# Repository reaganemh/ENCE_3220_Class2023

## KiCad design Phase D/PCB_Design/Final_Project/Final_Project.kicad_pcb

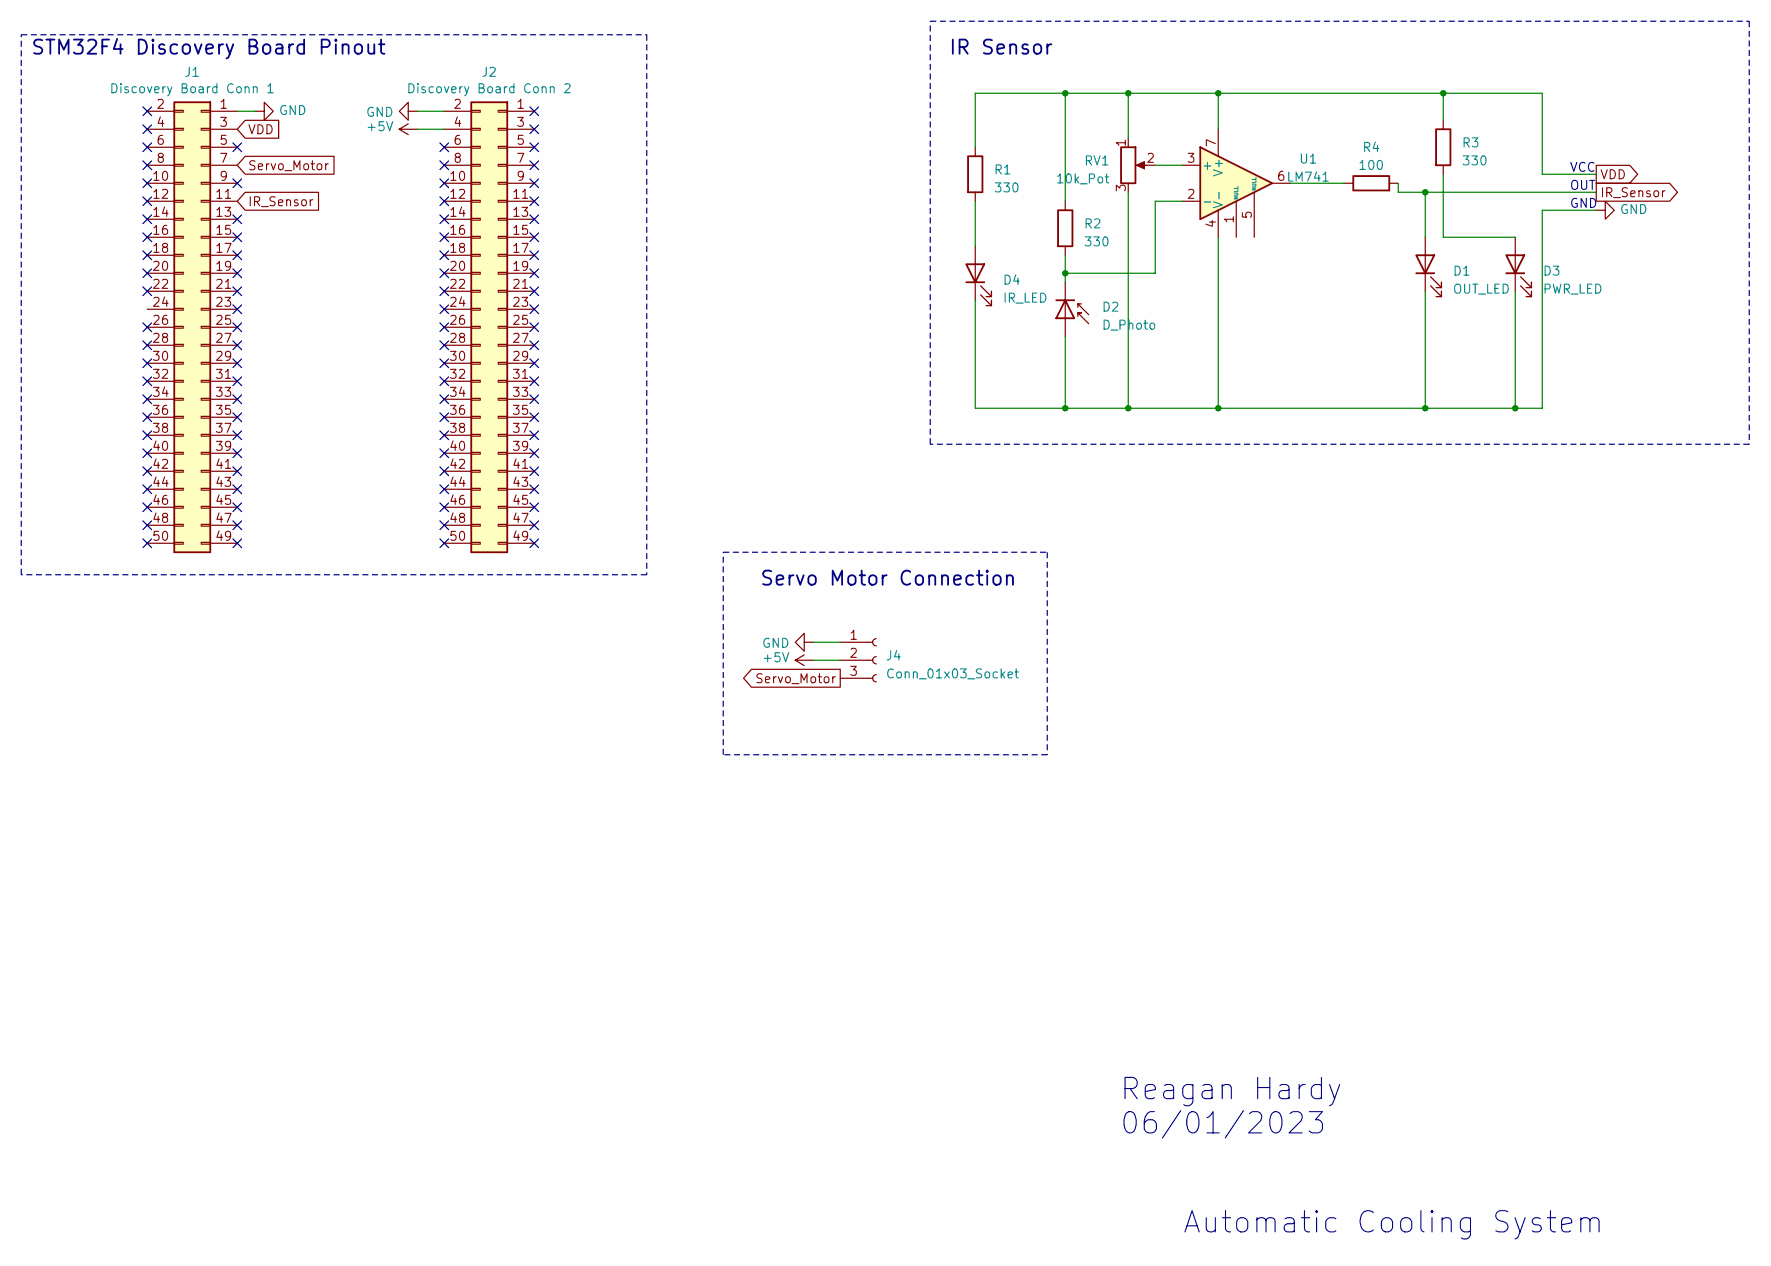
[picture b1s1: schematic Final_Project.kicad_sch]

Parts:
D1: OUT_LED; LED_0805_2012Metric_Pad1.15x1.40mm_HandSolder
D2: D_Photo; LED_D5.0mm_Horizontal_O1.27mm_Z3.0mm
D3: PWR_LED; LED_0805_2012Metric_Pad1.15x1.40mm_HandSolder
D4: IR_LED; LED_D5.0mm_Horizontal_O1.27mm_Z3.0mm
J1: Discovery Board Conn 1; PinSocket_2x25_P2.54mm_Vertical
J2: Discovery Board Conn 2; PinSocket_2x25_P2.54mm_Vertical
J4: Conn_01x03_Socket; PinSocket_1x03_P2.54mm_Vertical
R1, R2, R3: 330; R_0805_2012Metric
R4: 100; R_0805_2012Metric
RV1: 10k_Pot; Potentiometer_ACP_CA9-V10_Vertical_Hole
U1: LM741; SOIC-8_3.9x4.9mm_P1.27mm

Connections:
+5V: J2.4, J4.2
GND: D1.1 (K), D2.2 (A), D3.1 (K), D4.1 (K), J1.1, J2.2, J4.1, RV1.3, U1.4 (V-)
IR_Sensor: D1.2 (A), J1.11, R4.2
unnamed: D2.1 (K), R2.2, U1.2 (-)
unnamed: D3.2 (A), R3.2
unnamed: D4.2 (A), R1.2
unnamed: R4.1, U1.6
unnamed: RV1.2, U1.3 (+)
Servo_Motor: J1.7, J4.3
VDD: J1.3, R1.1, R2.1, R3.1, RV1.1, U1.7 (V+)

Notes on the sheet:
Automatic Cooling System
IR Sensor
Reagan Hardy 06/01/2023
VCC
GND
STM32F4 Discovery Board Pinout
Servo Motor Connection
OUT

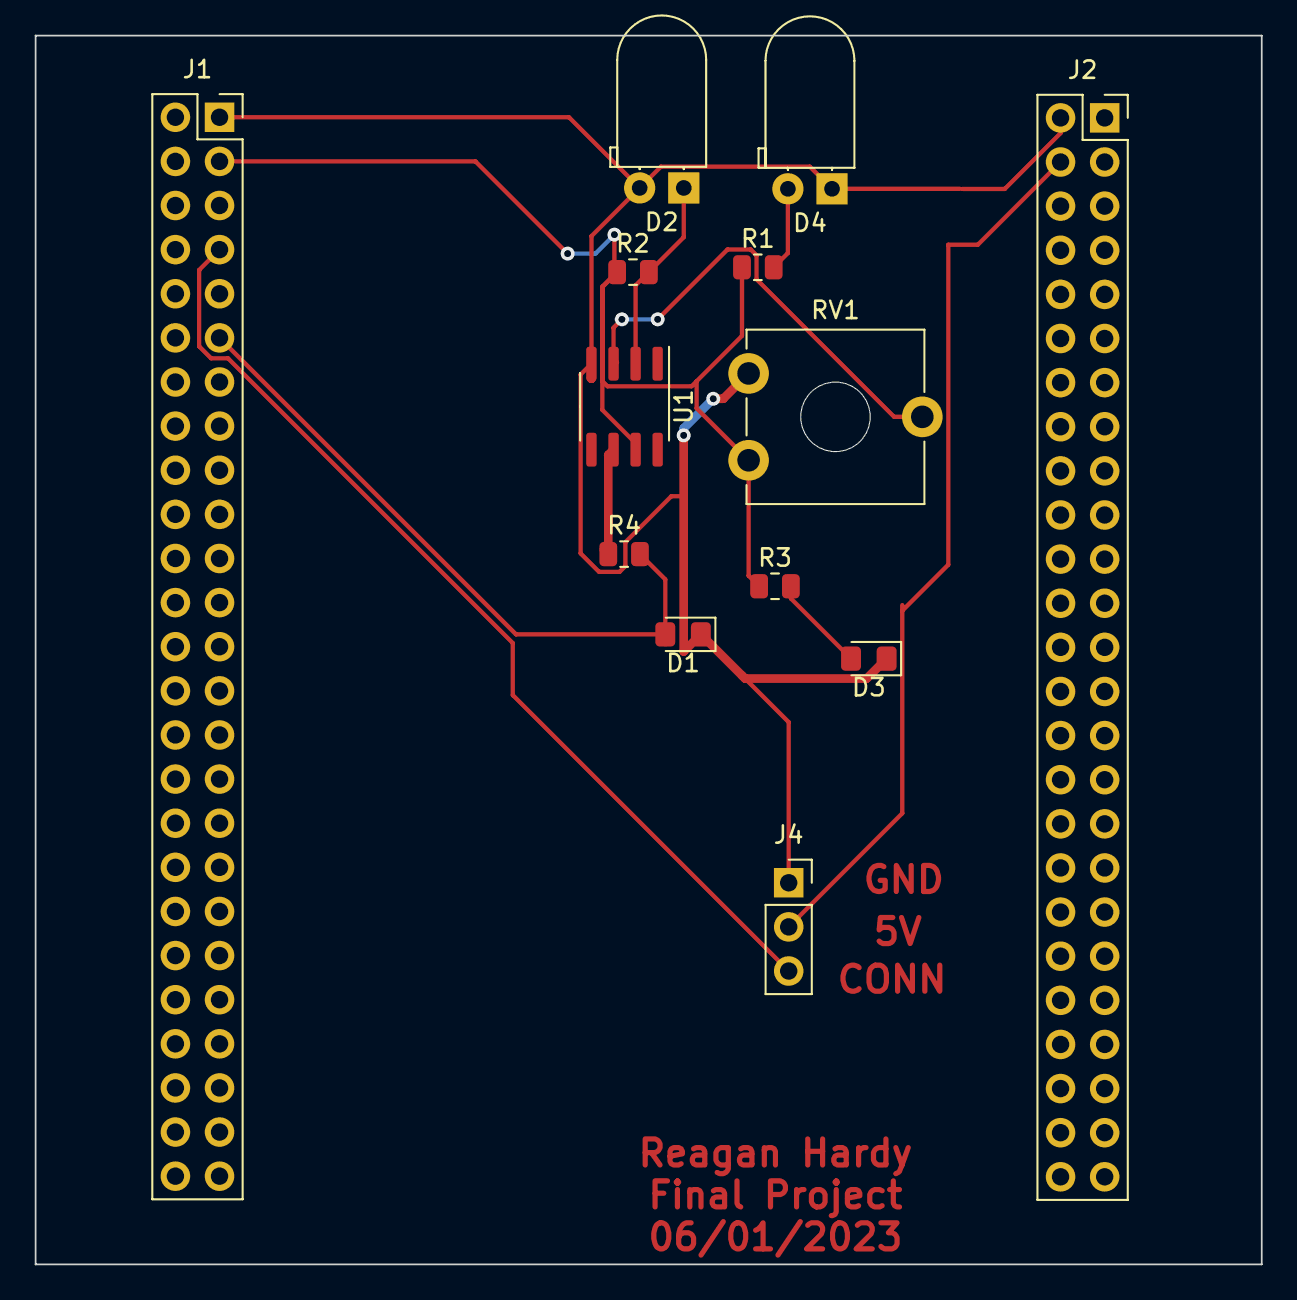
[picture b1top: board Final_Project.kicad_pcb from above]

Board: 2 copper layers, 70.6 x 70.7 mm, 13 parts (0 on the bottom side), 10 nets.

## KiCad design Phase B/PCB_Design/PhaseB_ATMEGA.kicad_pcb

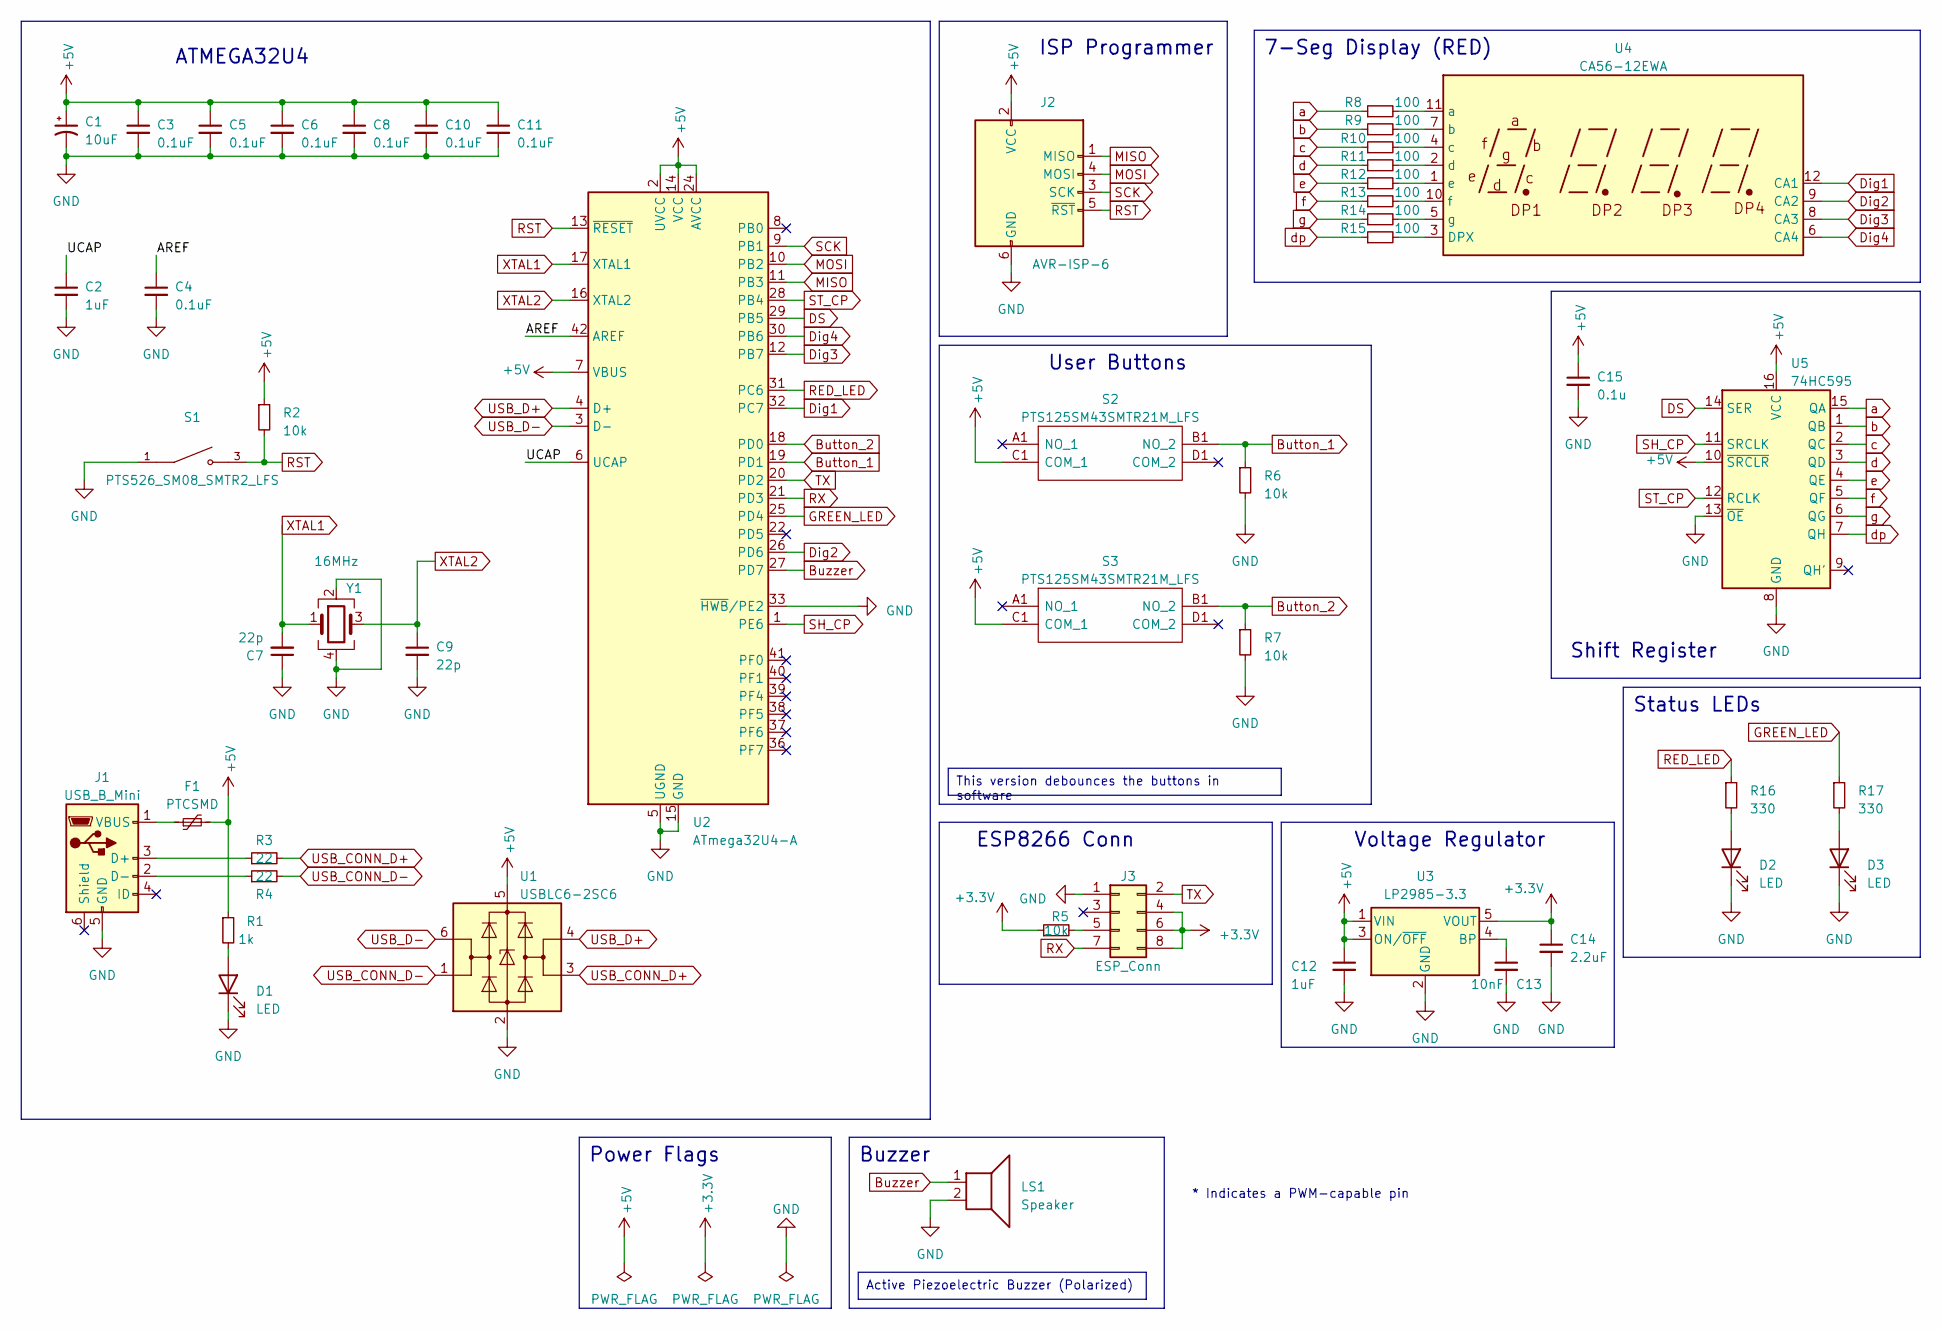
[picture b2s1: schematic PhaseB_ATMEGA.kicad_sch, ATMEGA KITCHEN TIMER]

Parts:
C1: 10uF; C_0805_2012Metric
C2, C12: 1uF; C_0603_1608Metric
C3, C4, C5, C6, C8, C10, C11: 0.1uF; C_0603_1608Metric
C7, C9: 22p; C_0603_1608Metric
C13: 10nF; C_0603_1608Metric
C14: 2.2uF; C_0603_1608Metric
C15: 0.1u; C_0603_1608Metric
D1, D2, D3: LED; LED_0805_2012Metric
F1: PTCSMD; Fuse_1812_4532Metric
J1: USB_B_Mini; USB_Mini-B_Lumberg_2486_01_Horizontal
J2: AVR-ISP-6; PinSocket_2x03_P2.54mm_Vertical
J3: ESP_Conn; PinSocket_2x04_P2.54mm_Vertical
LS1: Speaker; Buzzer_12x9.5RM7.6
R1: 1k; R_0603_1608Metric
R2, R5: 10k; R_0603_1608Metric
R3, R4: 22; R_0603_1608Metric
R6, R7: 10k; R_0805_2012Metric
R8, R9, R10, R11, R12, R13, R14, R15: 100; R_0805_2012Metric
R16, R17: 330; R_0805_2012Metric
S1: PTS526_SM08_SMTR2_LFS; PTS526_SMD_Button; PARTREV 20 mar 19
S2, S3: PTS125SM43SMTR21M_LFS; PTS125_SMD_Button; Manufacturer_Part_Number PTS125SM43SMTR21M LFS; Mouser Part Number 611-PTS125S43SMTRLFS
U1: USBLC6-2SC6; SOT-23-6
U2: ATmega32U4-A; TQFP-44_10x10mm_P0.8mm
U3: LP2985-3.3; SOT-23-5
U4: CA56-12EWA
U5: 74HC595; TSSOP-16_4.4x5mm_P0.65mm
Y1: 16MHz; Crystal_SMD_Abracon_ABM8G-4Pin_3.2x2.5mm

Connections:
+3.3V: C14.1, J3.4, J3.6, J3.8, R5.1, U3.5 (VOUT)
+5V: C1.1, C3.1, C5.1, C6.1, C8.1, C10.1, C11.1, C12.1, C15.1, F1.2, J2.2 (VCC), R1.1, R2.1, S2.C1 (COM_1), S3.C1 (COM_1), U1.5 (VBUS), U2.2 (UVCC), U2.7 (VBUS), U2.14 (VCC), U2.24 (AVCC), U2.34 (VCC), U2.44 (AVCC), U3.1 (VIN), U3.3 (ON/~OFF), U5.10 (~SRCLR), U5.16 (VCC)
/AREF: C4.1, U2.42 (AREF)
/UCAP: C2.1, U2.6 (UCAP)
Button_1: R6.1, S2.B1 (NO_2), U2.19 (PD1)
Button_2: R7.1, S3.B1 (NO_2), U2.18 (PD0)
Buzzer: LS1.1, U2.27 (PD7)
DS: U2.29 (PB5), U5.14 (SER)
Dig1: U2.32 (PC7), U4.12 (CA1)
Dig2: U2.26 (PD6), U4.9 (CA2)
Dig3: U2.12 (PB7), U4.8 (CA3)
Dig4: U2.30 (PB6), U4.6 (CA4)
GND: C1.2, C2.2, C3.2, C4.2, C5.2, C6.2, C7.1, C8.2, C9.2, C10.2, C11.2, C12.2, C13.2, C14.2, C15.2, D1.1 (K), D2.1 (K), D3.1 (K), J1.5 (GND), J2.6 (GND), J3.1, LS1.2, R6.2, R7.2, S1.1, U1.2 (GND), U2.5 (UGND), U2.15 (GND), U2.23 (GND), U2.33 (~HWB/PE2), U2.35 (GND), U2.43 (GND), U3.2 (GND), U5.8 (GND), U5.13 (~OE), Y1.2, Y1.4
GREEN_LED: R17.1, U2.25 (PD4)
MISO: J2.1 (MISO), U2.11 (PB3)
MOSI: J2.4 (MOSI), U2.10 (PB2)
unnamed: D1.2 (A), R1.2
unnamed: D2.2 (A), R16.2
unnamed: D3.2 (A), R17.2
unnamed: J1.3 (D+), R3.1
unnamed: J1.2 (D-), R4.1
unnamed: F1.1, J1.1 (VBUS)
unnamed: J3.5, R5.2
unnamed: C13.1, U3.4 (BP)
unnamed: R15.2, U4.3 (DPX)
unnamed: R8.2, U4.11 (a)
unnamed: R9.2, U4.7 (b)
unnamed: R10.2, U4.4 (c)
unnamed: R11.2, U4.2 (d)
unnamed: R12.2, U4.1 (e)
unnamed: R13.2, U4.10 (f)
unnamed: R14.2, U4.5 (g)
RED_LED: R16.1, U2.31 (PC6)
RST: J2.5 (~RST), R2.2, S1.3, U2.13 (~RESET)
RX: J3.7, U2.21 (PD3)
SCK: J2.3 (SCK), U2.9 (PB1)
SH_CP: U2.1 (PE6), U5.11 (SRCLK)
ST_CP: U2.28 (PB4), U5.12 (RCLK)
TX: J3.2, U2.20 (PD2)
USB_CONN_D+: R3.2, U1.3 (I/O2)
USB_CONN_D-: R4.2, U1.1 (I/O1)
USB_D+: U1.4 (I/O2), U2.4 (D+)
USB_D-: U1.6 (I/O1), U2.3 (D-)
XTAL1: C7.2, U2.17 (XTAL1), Y1.1
XTAL2: C9.1, U2.16 (XTAL2), Y1.3
a: R8.1, U5.15 (QA)
b: R9.1, U5.1 (QB)
c: R10.1, U5.2 (QC)
d: R11.1, U5.3 (QD)
dp: R15.1, U5.7 (QH)
e: R12.1, U5.4 (QE)
f: R13.1, U5.5 (QF)
g: R14.1, U5.6 (QG)

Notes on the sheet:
Active Piezoelectric Buzzer (Polarized)
This version debounces the buttons in software
ATMEGA32U4
Voltage Regulator
ESP8266 Conn
Shift Register
User Buttons
ISP Programmer
Power Flags
Status LEDs
Buzzer
7-Seg Display (RED)
* Indicates a PWM-capable pin

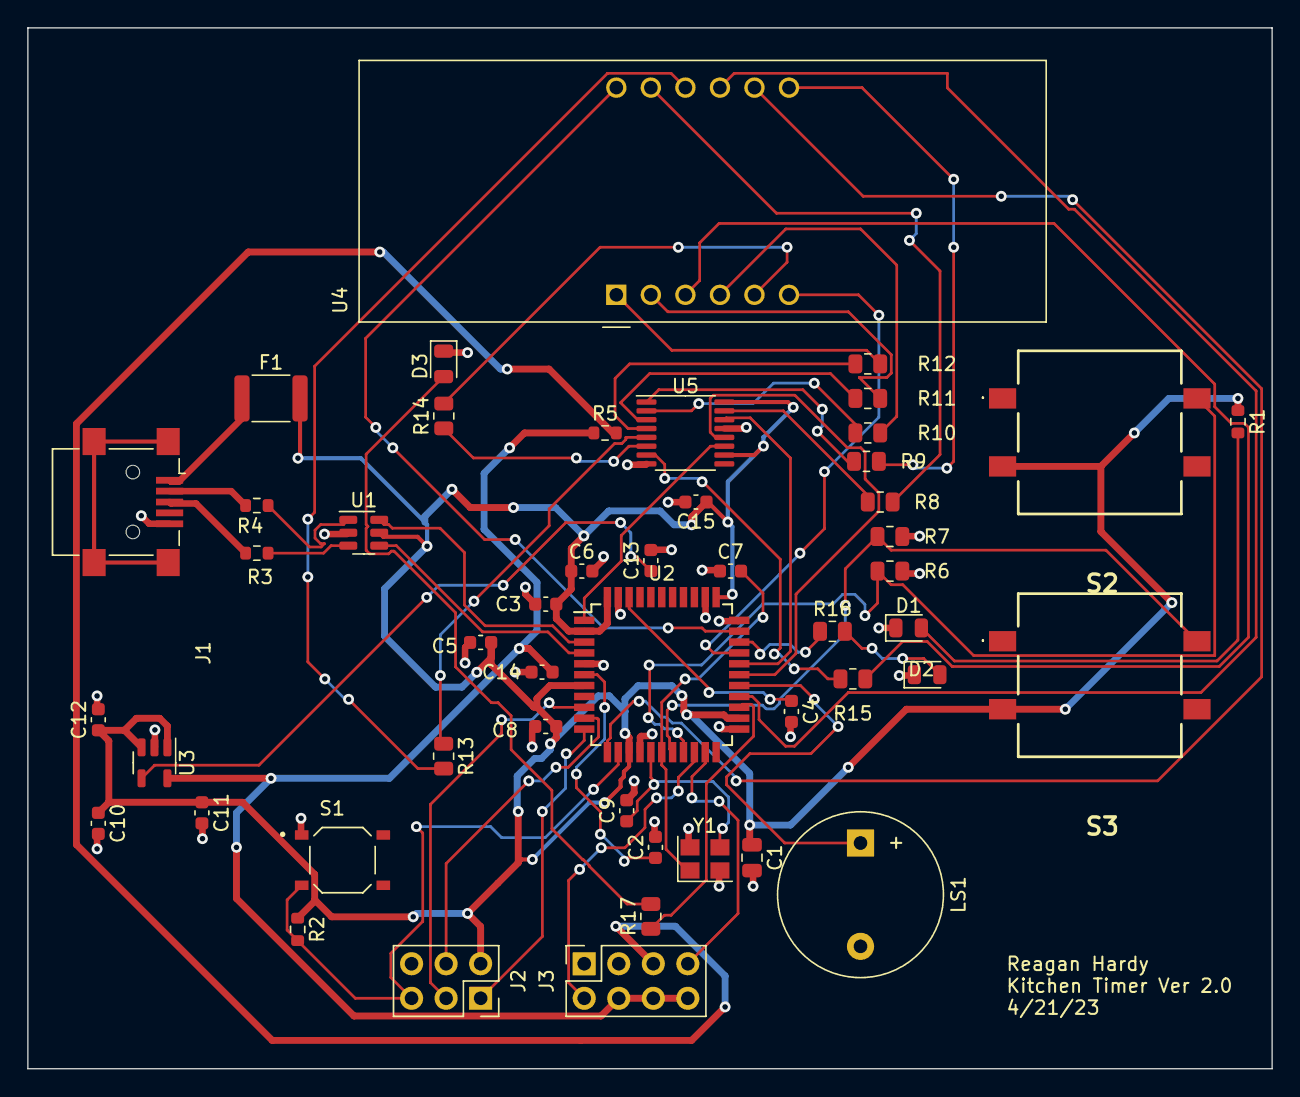
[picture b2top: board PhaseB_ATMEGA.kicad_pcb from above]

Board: 2 copper layers, 91.5 x 76.6 mm, 49 parts (0 on the bottom side), 53 nets.

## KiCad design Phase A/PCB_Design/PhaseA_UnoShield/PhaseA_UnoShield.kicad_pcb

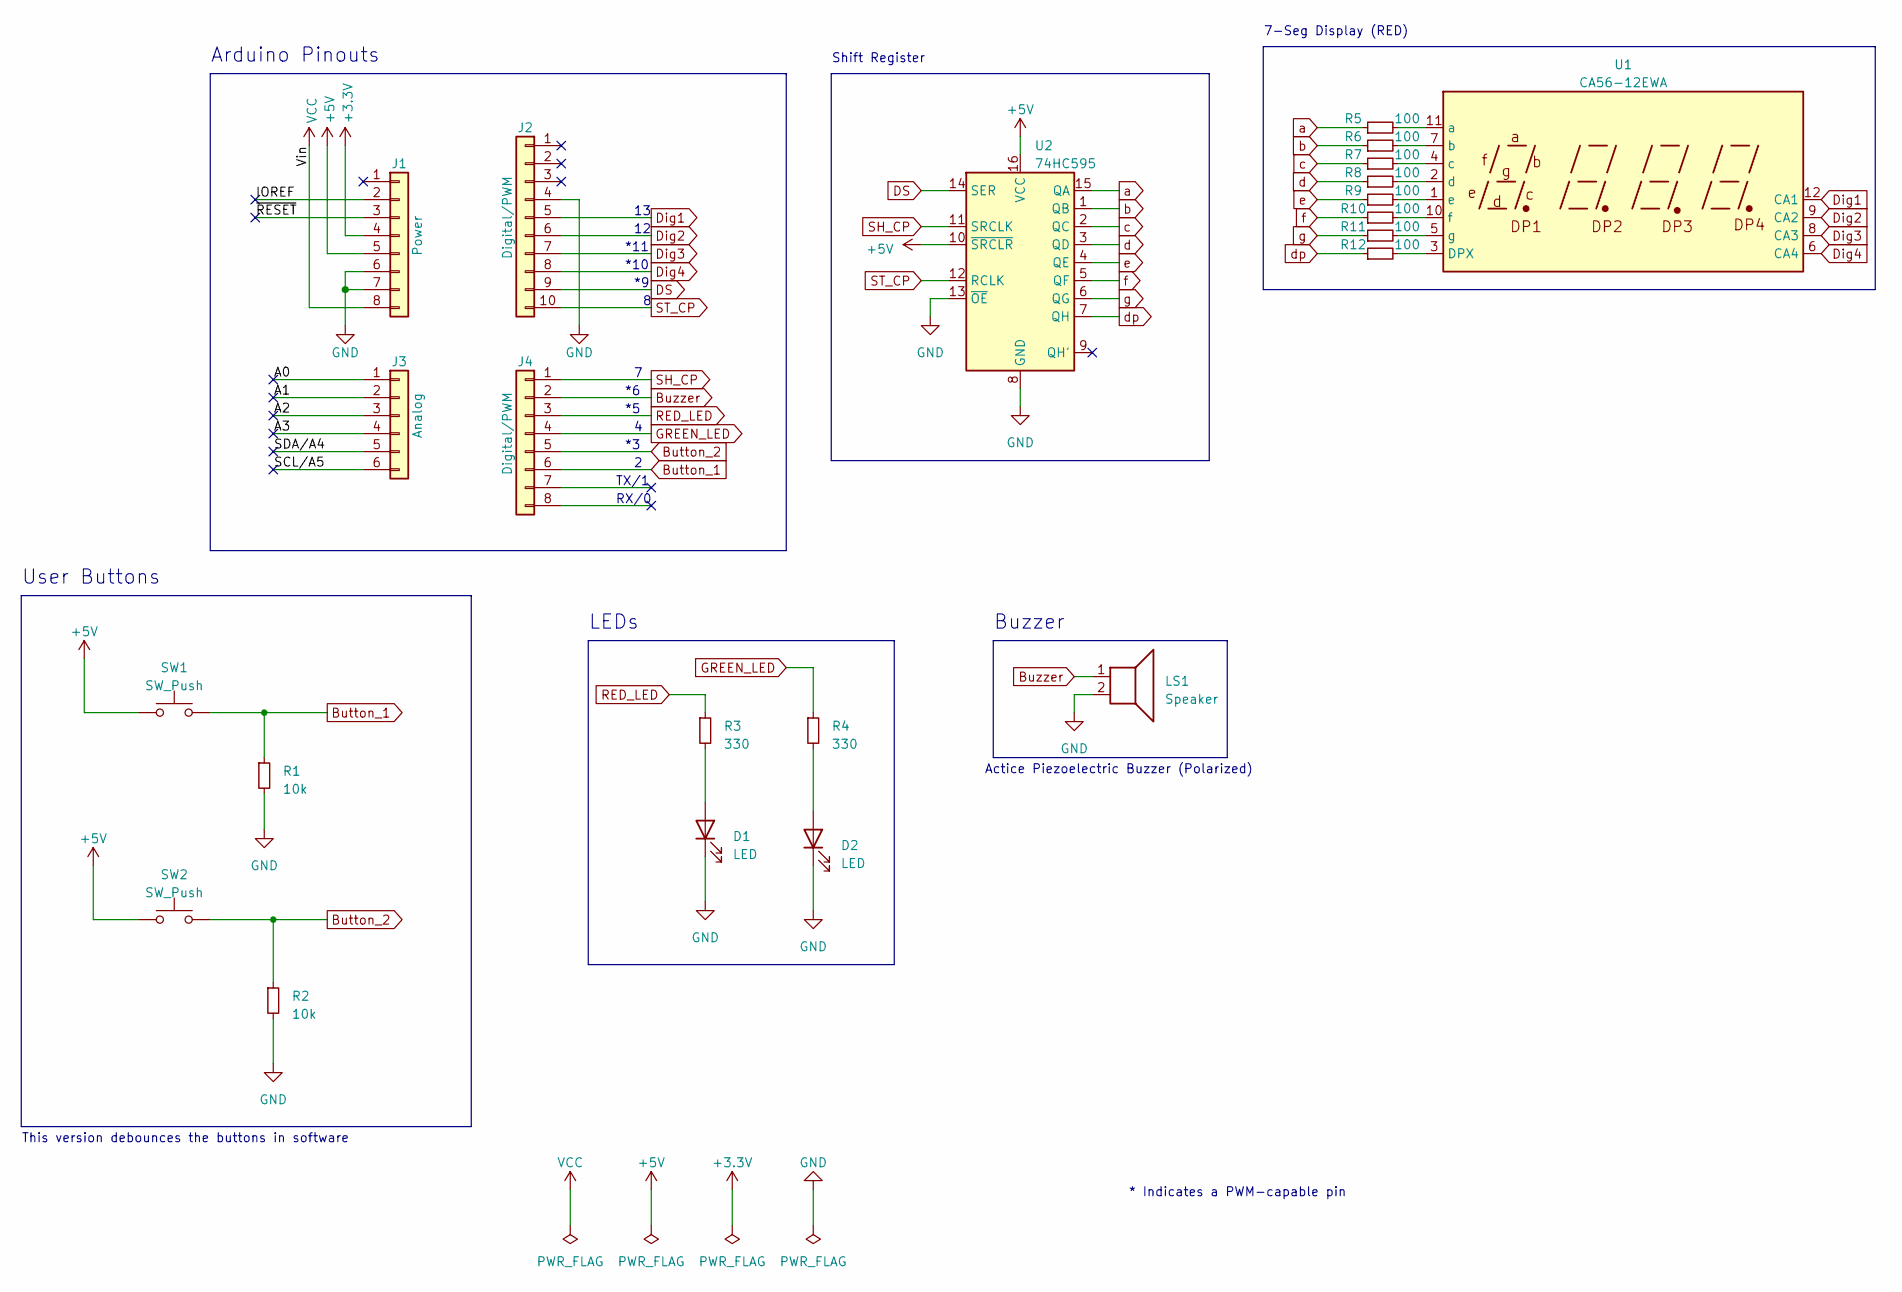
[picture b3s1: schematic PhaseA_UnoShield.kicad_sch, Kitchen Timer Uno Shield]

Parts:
D1, D2: LED; LED_D5.0mm
J1: Power; PinSocket_1x08_P2.54mm_Vertical
J2: Digital/PWM; PinSocket_1x10_P2.54mm_Vertical
J3: Analog; PinSocket_1x06_P2.54mm_Vertical
J4: Digital/PWM; PinSocket_1x08_P2.54mm_Vertical
LS1: Speaker; Buzzer_12x9.5RM7.6
R1, R2: 10k; R_Axial_DIN0207_L6.3mm_D2.5mm_P10.16mm_Horizontal
R3, R4: 330; R_Axial_DIN0207_L6.3mm_D2.5mm_P10.16mm_Horizontal
R5, R6, R7, R8, R9, R10, R11, R12: 100; R_Axial_DIN0207_L6.3mm_D2.5mm_P10.16mm_Horizontal
SW1, SW2: SW_Push; SW_PUSH-12mm
U1: CA56-12EWA
U2: 74HC595; DIP-16_W7.62mm_Socket_LongPads

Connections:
+3V3: J1.4
+5V: J1.5, SW1.1, SW2.1, U2.10 (~SRCLR), U2.16 (VCC)
/A0: J3.1
/A1: J3.2
/A2: J3.3
/A3: J3.4
/IOREF: J1.2
/SCL/A5: J3.6
/SDA/A4: J3.5
/~RESET: J1.3
Button_1: J4.6, R1.1, SW1.2
Button_2: J4.5, R2.1, SW2.2
Buzzer: J4.2, LS1.1
DS: J2.9, U2.14 (SER)
Dig1: J2.5, U1.12 (CA1)
Dig2: J2.6, U1.9 (CA2)
Dig3: J2.7, U1.8 (CA3)
Dig4: J2.8, U1.6 (CA4)
GND: D1.1 (K), D2.1 (K), J1.6, J1.7, J2.4, LS1.2, R1.2, R2.2, U2.8 (GND), U2.13 (~OE)
GREEN_LED: J4.4, R4.1
unnamed: D1.2 (A), R3.2
unnamed: D2.2 (A), R4.2
unnamed: R12.2, U1.3 (DPX)
unnamed: R5.2, U1.11 (a)
unnamed: R6.2, U1.7 (b)
unnamed: R7.2, U1.4 (c)
unnamed: R8.2, U1.2 (d)
unnamed: R9.2, U1.1 (e)
unnamed: R10.2, U1.10 (f)
unnamed: R11.2, U1.5 (g)
RED_LED: J4.3, R3.1
SH_CP: J4.1, U2.11 (SRCLK)
ST_CP: J2.10, U2.12 (RCLK)
VCC: J1.8
a: R5.1, U2.15 (QA)
b: R6.1, U2.1 (QB)
c: R7.1, U2.2 (QC)
d: R8.1, U2.3 (QD)
dp: R12.1, U2.7 (QH)
e: R9.1, U2.4 (QE)
f: R10.1, U2.5 (QF)
g: R11.1, U2.6 (QG)

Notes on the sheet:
This version debounces the buttons in software
7-Seg Display (RED)
TX/1
LEDs
Actice Piezoelectric Buzzer (Polarized)
User Buttons
Arduino Pinouts
RX/0
*11
* Indicates a PWM-capable pin
Shift Register
*10
Buzzer

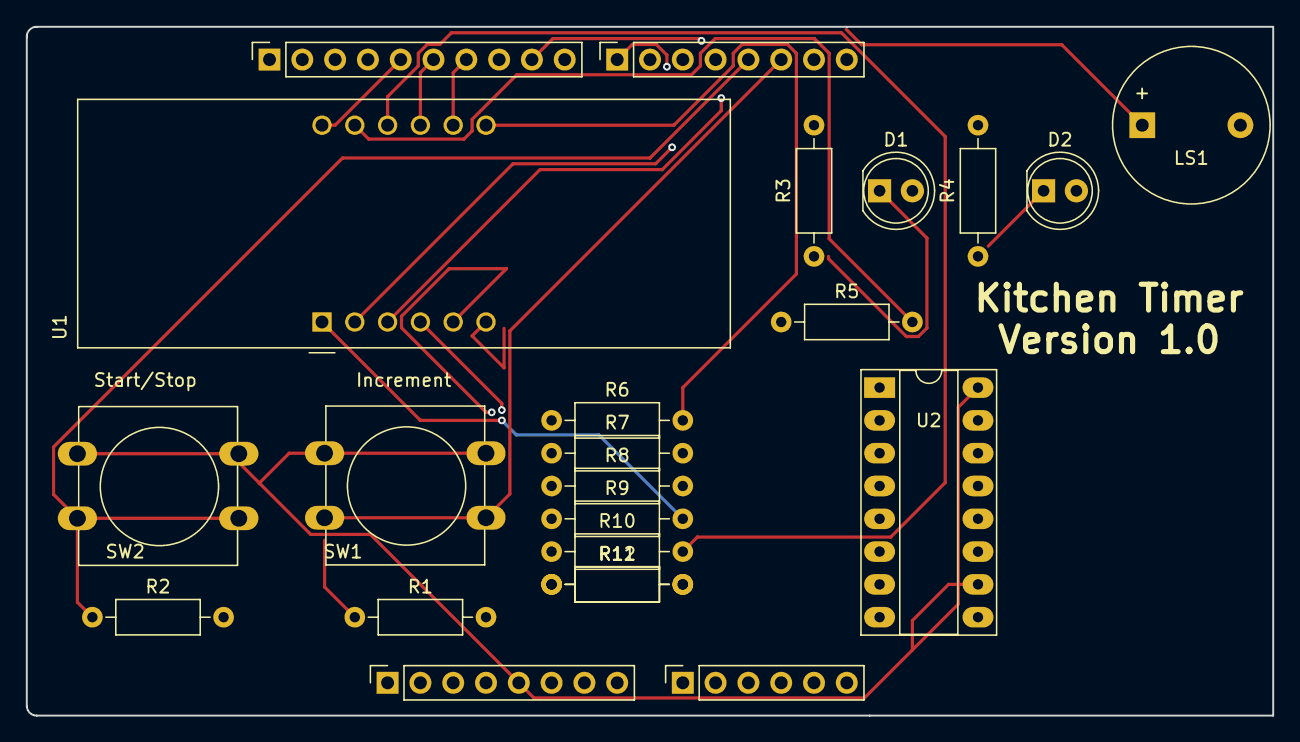
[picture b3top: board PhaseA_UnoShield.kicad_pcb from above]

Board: 2 copper layers, 96.5 x 53.3 mm, 23 parts (0 on the bottom side), 32 nets.

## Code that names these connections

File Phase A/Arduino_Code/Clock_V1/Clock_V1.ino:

#define BUTTON_1  2    //defines button_1 to pin 2
#define BUTTON_2  3    //defines button_2 to pin 3
#define GREEN_LED 4    //defines green_led to pin 4
#define RED_LED   5    //defines red_led to pin 5
#define BUZZER    6    //defines buzzer to pin 6

#define DATA      9    //defines data to pin 9
#define LATCH     8    //defines latch to pin 8
#define CLOCK     7    //defines clock to pin 7

#define DIGIT_4   10    //defines digit_4 to pin 10
#define DIGIT_3   11    //defines digit_3 to pin 11
#define DIGIT_2   12    //defines digit_2 to pin 12
#define DIGIT_1   13    //defines digit_1 to pin 13
 
unsigned char table[]=
{0x3f,0x06,0x5b,0x4f,0x66,0x6d,0x7d,0x07,0x7f,0x6f,0x77,0x7c
,0x39,0x5e,0x79,0x71,0x00};

void setup() {
  // LEDs Pins
  pinMode(RED_LED, OUTPUT);
  pinMode(GREEN_LED, OUTPUT);

  // Button Pins
  pinMode(BUTTON_1, INPUT_PULLUP);
  attachInterrupt(digitalPinToInterrupt(BUTTON_1), Button_1_ISR, CHANGE);
  pinMode(BUTTON_2, INPUT_PULLUP);
  attachInterrupt(digitalPinToInterrupt(BUTTON_2), Button_2_ISR, CHANGE);

  // Buzer Pins
  //pinMode(BUZZER, OUTPUT);

  // 7-Seg Display
  pinMode(DIGIT_1, OUTPUT);
  pinMode(DIGIT_2, OUTPUT);
  pinMode(DIGIT_3, OUTPUT);
  pinMode(DIGIT_4, OUTPUT);

  // Shift Register Pins
  pinMode(LATCH, OUTPUT);
  pinMode(CLOCK, OUTPUT);
  pinMode(DATA, OUTPUT);

  disp_off();  // turn off the display

  // Initialize Timer1 (16bit) -> Used for clock
  // Speed of Timer1 = 16MHz/256 = 62.5 KHz
  noInterrupts();         // disable all interrupts  
  TCCR1A = 0;
  TCCR1B = 0;
  OCR1A = reload_timer_1; // compare match register 16MHz/256
  TCCR1B |= (1<<WGM12);   // CTC mode
  TCCR1B |= (1<<CS12);    // 256 prescaler 
  TIMSK1 |= (1<<OCIE1A);  // enable timer compare interrupt

  // Initialize Timer2 (8bit) -> Used to refresh display
  // Speed of Timer2 = 16MHz/1024 = 15.625 KHz
  TCCR2A = 0;
  TCCR2B = 0;
  OCR2A = reload_timer_2;                     // max value 2^8 - 1 = 255
  TCCR2A |= (1<<WGM21);
  TCCR2B = (1<<CS22) | (1<<CS21) | (1<<CS20); // 1204 prescaler
  TIMSK2 |= (1<<OCIE2A);
  interrupts();                               // enable all interrupts
}

void Display(unsigned char num)
{
  digitalWrite(LATCH, LOW);
  shiftOut(DATA, CLOCK, MSBFIRST, table[num]);
  digitalWrite(LATCH, HIGH);
}

void Display_Numbers()
{
  Display(count);

  // Reset Counter
  if(count == 16)
  {
    count = 0;
  }
}

void disp_off()
{
   digitalWrite(DIGIT_1, HIGH);
   digitalWrite(DIGIT_2, HIGH);
   digitalWrite(DIGIT_3, HIGH);
   digitalWrite(DIGIT_4, HIGH);
}

void Buttons()
{
  unsigned int buttonState = 0;

  buttonState = digitalRead(BUTTON_1);
  digitalWrite(RED_LED, buttonState);

  buttonState = digitalRead(BUTTON_2);
  digitalWrite(GREEN_LED, buttonState);
}

void Active_Buzzer()
{
  unsigned char i;
  unsigned char sleep_time = 1;

  for(i=0;i<100;i++)
  {
    digitalWrite(BUZZER,HIGH);
    delay(sleep_time);
    digitalWrite(BUZZER,LOW);
    delay(sleep_time);
  }
}

void BlinkLEDs()
{
  digitalWrite(RED_LED,HIGH);
  digitalWrite(GREEN_LED,LOW);
  delay(500);
  digitalWrite(RED_LED,LOW);
  digitalWrite(GREEN_LED,HIGH);
  delay(500);
}

void Display_Numbers()
{
  unsigned char sleep_time = 100;
  Display(0);
  delay(sleep_time);
  Display(1);
  delay(sleep_time);
  Display(2);
  delay(sleep_time);

}

void loop() {
  //BlinkLEDs();
  Display_Numbers();
  //Active_Buzzer;
  Buttons();
}

ISR(TIMER2_COMPA_vect)   // Timer1 interrupt service routine (ISR)
{
  disp_off();  // turn off the display
  OCR2A = reload_timer_2;
 
  switch (current_digit)
  {
    case 1:
      Display(count / 1000);   // prepare to display digit 1 (most left)
      digitalWrite(DIGIT_1, LOW);  // turn on digit 1
      break;
 
    case 2:
      Display( (count / 100) % 10 );   // prepare to display digit 2
      digitalWrite(DIGIT_2, LOW);     // turn on digit 2
      break;
 
    case 3:
      Display( (count / 10) % 10 );   // prepare to display digit 3
      digitalWrite(DIGIT_3, LOW);    // turn on digit 3
      break;
 
    case 4:
      Display(count % 10); // prepare to display digit 4 (most right)
      digitalWrite(DIGIT_4, LOW);  // turn on digit 4
  }
 
  current_digit = (current_digit % 4) + 1;
}

ISR(TIMER1_COMPA_vect)
{
  count++;
  OCR1A = reload_timer_1;

  if(count > 9999)
      count = 0;
}

void loop() 
{
  // Attend Button 1
  if(isr_1_flag == 1)
  {
    // Reset ISR Flag
    isr_1_flag = 0;

    // Code
    buttonState = digitalRead(BUTTON_1);
    digitalWrite(RED_LED, buttonState);

    // Increment Clock
    count++;
  }

  // Attend Button 2
  if(isr_2_flag == 1)
  {
    // Reset ISR Flag
    isr_2_flag = 0;

    // Code
    buttonState = digitalRead(BUTTON_2);
    digitalWrite(GREEN_LED, buttonState);

    // Reset Clock
    count = 0;
    TCCR1B = 0; // stop clock
    TIMSK1 = 0; // cancel clock timer interrupt  
  }
}

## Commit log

2023-04-13 Test
2023-04-13 Yeah
2023-04-13 Kitchen Timer
2023-04-21 PhaseB
2023-05-03 phase b
2023-05-23 phase c
2023-06-01 final project
